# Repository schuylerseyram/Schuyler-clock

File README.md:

# emshilton-clock
 My First HPS clock.

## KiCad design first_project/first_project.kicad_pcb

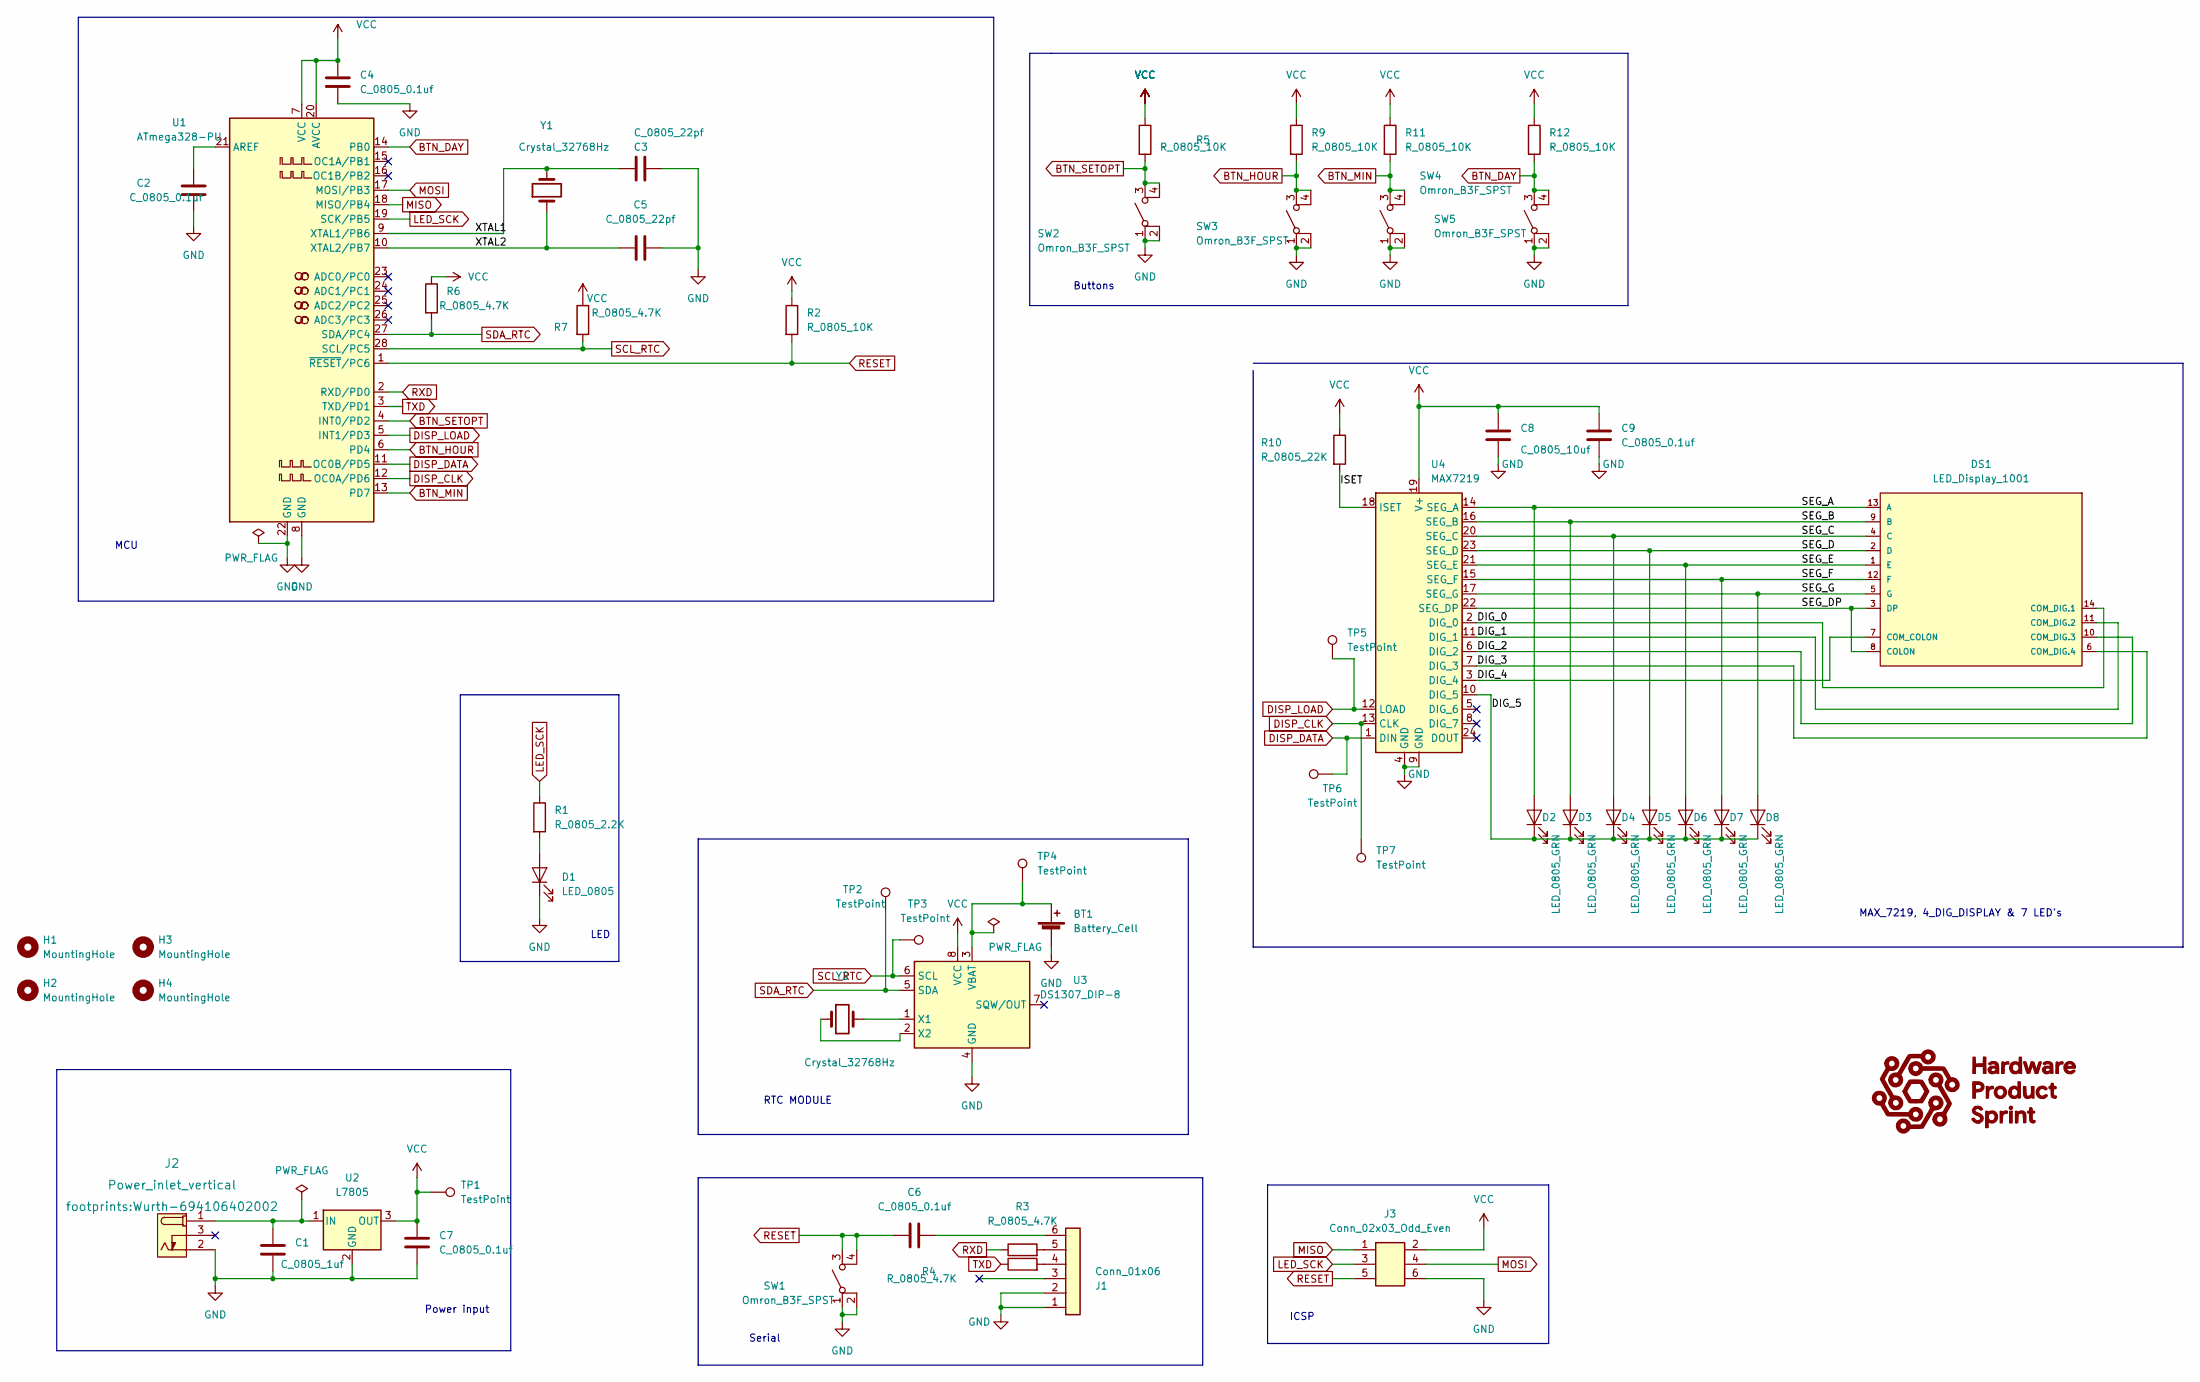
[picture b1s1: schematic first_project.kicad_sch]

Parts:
BT1: Battery_Cell; BatteryHolder_Keystone_106_1x20mm; MPN BS-7; Digikey PN BS-7-ND
C1: C_0805_1uf; C_0805_2012Metric; Voltage N/A; Tolerance N/A; MPN CC0805KKX7R8BB105; Digikey PN 311-1456-1-ND
C2, C4, C6, C7, C9: C_0805_0.1uf; C_0805_2012Metric; Voltage N/A; Tolerance N/A; MPN 08055C104KAT2A; Digikey PN 478-1395-1-ND
C3, C5: C_0805_22pf; C_0805_2012Metric; Voltage N/A; Tolerance N/A; MPN CC0805JRNPO9BN220; Digikey PN 311-1103-1-ND
C8: C_0805_10uf; C_0805_2012Metric; Voltage N/A; Tolerance N/A; MPN GRM21BR61E106KA73L; Digikey PN 490-5523-1-ND
D1: LED_0805; LED_0805_2012Metric; MPN 150080RS75000; Digikey PN 732-4984-1-ND
D2, D3, D4, D5, D6, D7, D8: LED_0805_GRN; LED_0805_2012Metric; MPN 150080VS75000; Digikey PN 732-4986-1-ND
DS1: LED_Display_1001; Adafruit-1001-0-0-MFG; forward voltage 3.2V; reverse voltage 5V; mouser part number 485-1001; digikey description WHITE 7-SEGMENT CLOCK DISPLAY
H1, H2, H3, H4: MountingHole; MountingHole_3.2mm_M3
J1: Conn_01x06; PinHeader_1x06_P2.54mm_Vertical; MPN 61300611121; Digikey PN 732-5319-ND
J2: Power_inlet_vertical; Wurth-694106402002; MPN 694106402002; Digikey PN 732-5931-ND
J3: Conn_02x03_Odd_Even; PinHeader_2x03_P2.54mm_Vertical; MPN PRPC003DAAN-RC; Digikey PN S2011EC-03-ND
R1: R_0805_2.2K; R_0805_2012Metric; Tolerance N/A; MPN N/A; Digikey PN 311-2.20KCRCT-ND
R2, R5, R9, R11, R12: R_0805_10K; R_0805_2012Metric; Tolerance N/A; MPN RC0805FR-0710KL; Digikey PN 311-10.0KCRCT-ND
R3, R4, R6, R7: R_0805_4.7K; R_0805_2012Metric; Tolerance N/A; MPN RC0805FR-074K7L; Digikey PN 311-4.70KCRCT-ND
R10: R_0805_22K; R_0805_2012Metric; Tolerance N/A; MPN RC0805FR-0722KL; Digikey PN 311-22.0KCRCT-ND
SW1, SW2, SW3, SW4, SW5: Omron_B3F_SPST; SW_SPST_Omron_B3FS-100xP; MPN B3FS-1000P; Digikey PN SW423CT-ND
TP1, TP2, TP3, TP4, TP5, TP6, TP7: TestPoint; TestPoint_THTPad_D2.0mm_Drill1.0mm
U1: ATmega328-PU; DIP-28_W7.62mm; MPN ED281DT; Digikey PN ED3050-5-ND
U2: L7805; TO-252-2; MPN L7805CDT-TR; Digikey PN 497-7255-1-ND
U3: DS1307_DIP-8; DIP-8_W7.62mm; MPN A 08-LC-TT; Digikey PN AE9986-ND
U4: MAX7219; DIP-24_W7.62mm; MPN ED241DT; Digikey PN ED3049-5-ND
Y1, Y2: Crystal_32768Hz; Crystal_SMD_2Pin_3.2x1.5mm; MPN Q 0,032768-JTX310-12,5-20-T1-HMR-50K-LF; Digikey PN 1908-1314-1-ND

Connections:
/DIG_0: DS1.14 (COM_DIG.1), U4.2 (DIG_0)
/DIG_1: DS1.11 (COM_DIG.2), U4.11 (DIG_1)
/DIG_2: DS1.10 (COM_DIG.3), U4.6 (DIG_2)
/DIG_3: DS1.6 (COM_DIG.4), U4.7 (DIG_3)
/DIG_4: DS1.7 (COM_COLON), U4.3 (DIG_4)
/DIG_5: D2.1 (K), D3.1 (K), D4.1 (K), D5.1 (K), D6.1 (K), D7.1 (K), D8.1 (K), U4.10 (DIG_5)
/ISET: R10.2, U4.18 (ISET)
/SEG_A: D2.2 (A), DS1.13 (A), U4.14 (SEG_A)
/SEG_B: D3.2 (A), DS1.9 (B), U4.16 (SEG_B)
/SEG_C: D4.2 (A), DS1.4 (C), U4.20 (SEG_C)
/SEG_D: D5.2 (A), DS1.2 (D), U4.23 (SEG_D)
/SEG_DP: DS1.3 (DP), DS1.8 (COLON), U4.22 (SEG_DP)
/SEG_E: D6.2 (A), DS1.1 (E), U4.21 (SEG_E)
/SEG_F: D7.2 (A), DS1.12 (F), U4.15 (SEG_F)
/SEG_G: D8.2 (A), DS1.5 (G), U4.17 (SEG_G)
/XTAL1: C3.2, U1.9 (XTAL1/PB6), Y1.2
/XTAL2: C5.1, U1.10 (XTAL2/PB7), Y1.1
BTN_DAY: R12.2, SW5.3 (B), SW5.4 (B), U1.14 (PB0)
BTN_HOUR: R9.2, SW3.3 (B), SW3.4 (B), U1.6 (PD4)
BTN_MIN: R11.2, SW4.3 (B), SW4.4 (B), U1.13 (PD7)
BTN_SETOPT: R5.2, SW2.3 (B), SW2.4 (B), U1.4 (INT0/PD2)
DISP_CLK: TP7.1, U1.12 (OC0A/PD6), U4.13 (CLK)
DISP_DATA: TP6.1, U1.11 (OC0B/PD5), U4.1 (DIN)
DISP_LOAD: TP5.1, U1.5 (INT1/PD3), U4.12 (LOAD)
GND: BT1.2 (-), C1.2, C2.2, C3.1, C4.2, C5.2, C7.2, C8.2, C9.2, D1.1 (K), J1.1, J1.2, J2.2 (OUT), J3.6, SW1.1 (A), SW1.2 (A), SW2.1 (A), SW2.2 (A), SW3.1 (A), SW3.2 (A), SW4.1 (A), SW4.2 (A), SW5.1 (A), SW5.2 (A), U1.8 (GND), U1.22 (GND), U2.2 (GND), U3.4 (GND), U4.4 (GND), U4.9 (GND)
LED_SCK: J3.3, R1.1, U1.19 (SCK/PB5)
MISO: J3.1, U1.18 (MISO/PB4)
MOSI: J3.4, U1.17 (MOSI/PB3)
unnamed: BT1.1 (+), TP4.1, U3.3 (VBAT)
unnamed: C1.1, J2.1 (POLE), U2.1 (IN)
unnamed: C2.1, U1.21 (AREF)
unnamed: C6.2, J1.6
unnamed: D1.2 (A), R1.2
unnamed: J1.4, R4.2
unnamed: J1.5, R3.2
unnamed: U3.1 (X1), Y2.2
unnamed: U3.2 (X2), Y2.1
RESET: C6.1, J3.5, R2.2, SW1.3 (B), SW1.4 (B), U1.1 (~RESET/PC6)
RXD: R3.1, U1.2 (RXD/PD0)
SCL_RTC: R7.2, TP3.1, U1.28 (SCL/PC5), U3.6 (SCL)
SDA_RTC: R6.2, TP2.1, U1.27 (SDA/PC4), U3.5 (SDA)
TXD: R4.1, U1.3 (TXD/PD1)
VCC: C4.1, C7.1, C8.1, C9.1, J3.2, R2.1, R5.1, R6.1, R7.1, R9.1, R10.1, R11.1, R12.1, TP1.1, U1.7 (VCC), U1.20 (AVCC), U2.3 (OUT), U3.8 (VCC), U4.19 (V+)

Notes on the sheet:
Power input
ICSP
MAX_7219, 4_DIG_DISPLAY & 7 LED's
RTC MODULE
MCU
Buttons
LED
Serial

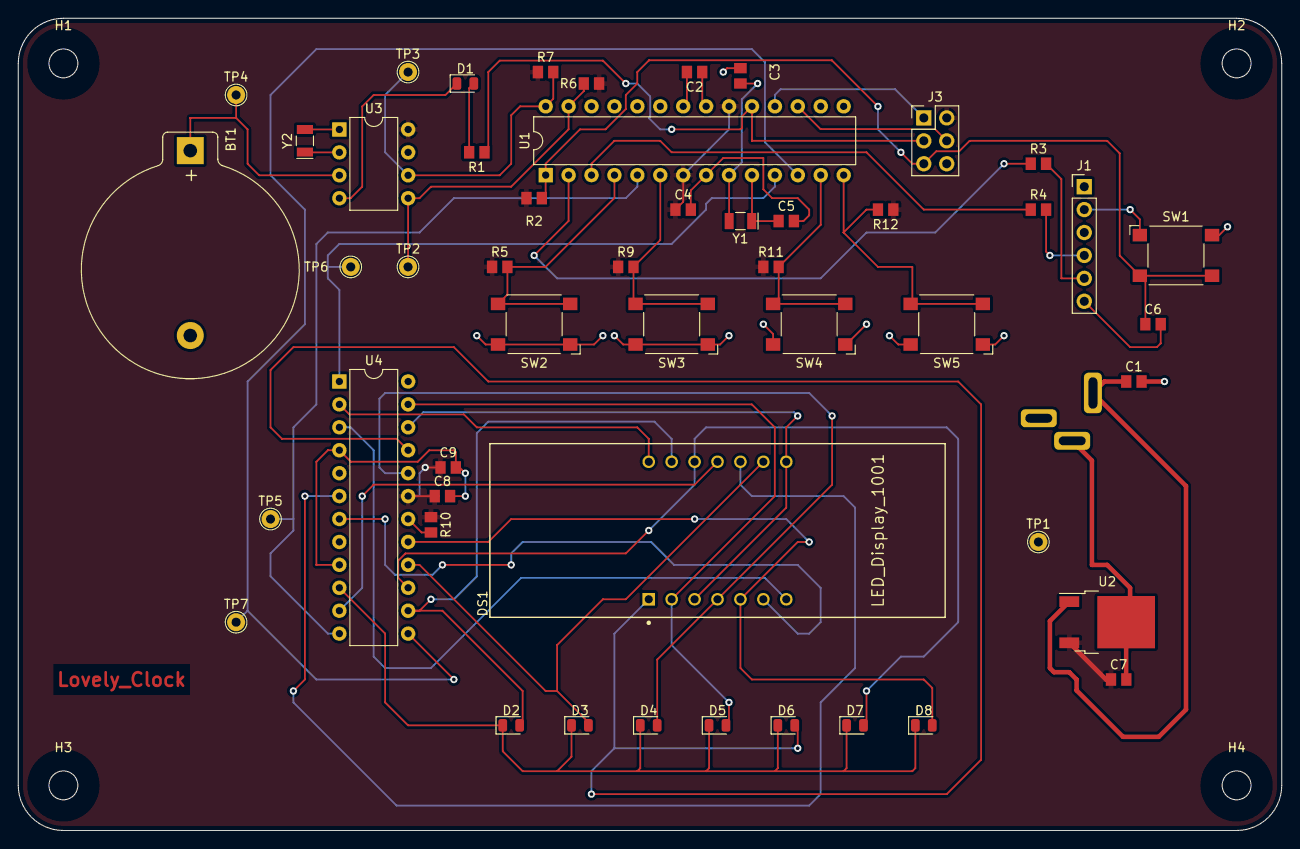
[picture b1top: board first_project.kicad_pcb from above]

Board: 2 copper layers, 140.0 x 90.0 mm, 55 parts (1 on the bottom side), 43 nets.

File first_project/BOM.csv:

"Id";"Designator";"Package";"Quantity";"Designation";"Supplier and ref";
1;"C7,C9,C2,C6,C4";"C_0805_2012Metric";5;"C_0805_0.1uf";;;
2;"Y1,Y2";"Crystal_SMD_2Pin_3.2x1.5mm";2;"Crystal_32768Hz";;;
3;"H4,H2,H3,H1";"MountingHole_3.2mm_M3";4;"MountingHole";;;
4;"D7,D5,D8,D2,D3,D6,D4";"LED_0805_2012Metric";7;"LED_0805_GRN";;;
5;"U4";"DIP-24_W7.62mm";1;"MAX7219";;;
6;"TP2,TP6,TP4,TP7,TP1,TP3,TP5";"TestPoint_THTPad_D2.0mm_Drill1.0mm";7;"TestPoint";;;
7;"C8";"C_0805_2012Metric";1;"C_0805_10uf";;;
8;"SW1,SW2,SW3,SW4,SW5";"SW_SPST_Omron_B3FS-100xP";5;"Omron_B3F_SPST";;;
9;"R6,R3,R4,R7";"R_0805_2012Metric";4;"R_0805_4.7K";;;
10;"R2,R9,R12,R5,R11";"R_0805_2012Metric";5;"R_0805_10K";;;
11;"J1";"PinHeader_1x06_P2.54mm_Vertical";1;"Conn_01x06";;;
12;"C5,C3";"C_0805_2012Metric";2;"C_0805_22pf";;;
13;"U3";"DIP-8_W7.62mm";1;"DS1307_DIP-8";;;
14;"D1";"LED_0805_2012Metric";1;"LED_0805";;;
15;"BT1";"BatteryHolder_Keystone_106_1x20mm";1;"Battery_Cell";;;
16;"R1";"R_0805_2012Metric";1;"R_0805_2.2K";;;
17;"R10";"R_0805_2012Metric";1;"R_0805_22K";;;
18;"C1";"C_0805_2012Metric";1;"C_0805_1uf";;;
19;"U2";"TO-252-2";1;"L7805";;;
20;"DS1";"Adafruit-1001-0-0-MFG";1;"LED_Display_1001";;;
21;"J3";"PinHeader_2x03_P2.54mm_Vertical";1;"Conn_02x03_Odd_Even";;;
22;"U1";"DIP-28_W7.62mm";1;"ATmega328-PU";;;
23;"J2";"Wurth-694106402002";1;"Power_inlet_vertical";;;

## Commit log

2022-05-30 first project
2022-06-12 Blink speed changed and schematics
    Blink speed is faster and basic schematics made by copying slide 39
2022-06-14 Few changes
2022-06-19 Week 2 changes
    Updated schematic.
2022-06-22 Schematic update
2022-07-04 New file
2022-07-04 updated with pcb
2022-07-05 firmware upload
2022-07-11 pcb routing
2022-07-11 first fully connected pcb. very terrible
2022-07-18 new routing + gerber
2022-07-21 final. I hope
2022-07-22 final gerber hopefully
2022-07-23 new changes
2022-07-23 gerber changes
